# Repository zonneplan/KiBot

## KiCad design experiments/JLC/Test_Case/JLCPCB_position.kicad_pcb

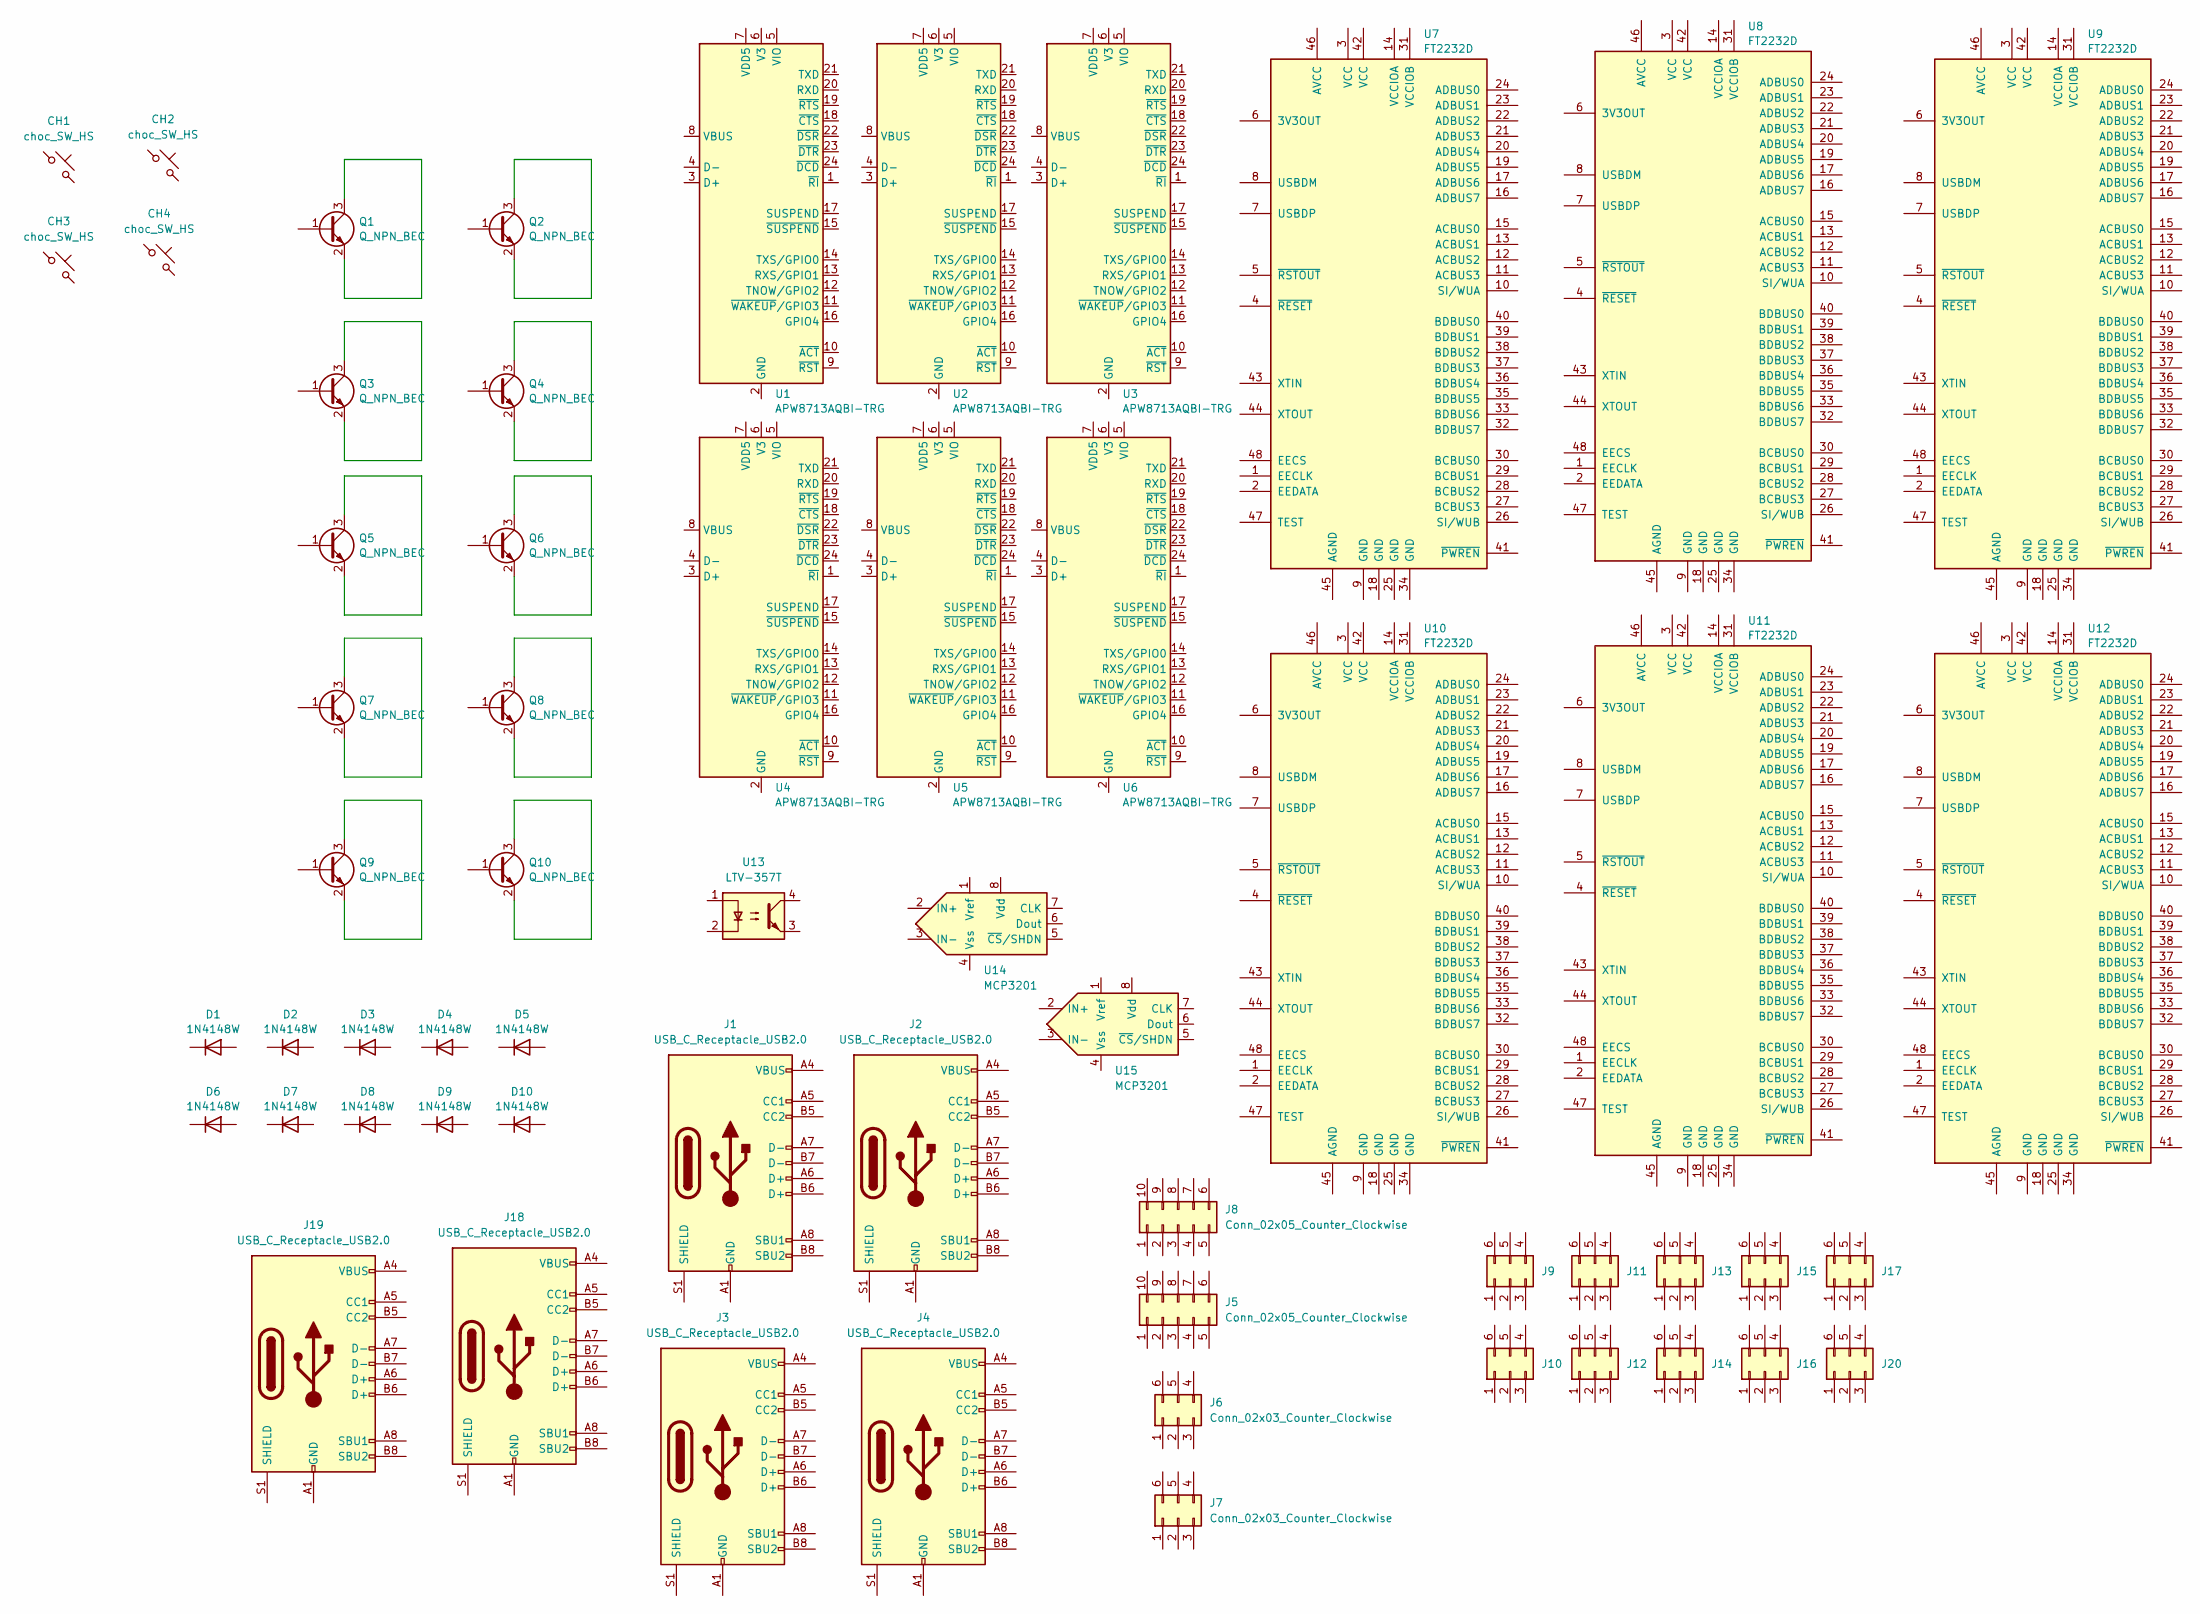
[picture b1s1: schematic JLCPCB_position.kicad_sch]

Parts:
CH1, CH2, CH3, CH4: choc_SW_HS; SW_choc_v1_HS_1u; LCSC C5333465
D1, D2, D3, D4, D5, D6, D7, D8, D9, D10: 1N4148W; D_SOD-123; LCSC C81598
J1, J2, J3, J4, J18, J19: USB_C_Receptacle_USB2.0; USB_C_Receptacle_XKB_U262-16XN-4BVC11; LCSC C319148
J5, J8: Conn_02x05_Counter_Clockwise; PinHeader_2x05_P1.27mm_Vertical; LCSC C2935953
J6, J7, J9, J10, J11, J12, J13, J14, J15, J16, J17, J20: Conn_02x03_Counter_Clockwise; PinHeader_2x03_P1.27mm_Vertical; LCSC C2935951
Q1, Q2, Q3, Q4, Q5, Q6, Q7, Q8, Q9, Q10: Q_NPN_BEC; SOT-23-3; LCSC C8667
U1, U2, U3, U4, U5, U6: APW8713AQBI-TRG; QFN-24-1EP_4x4mm_P0.5mm_EP2.6x2.6mm; LCSC C122485
U7, U8, U9, U10, U11, U12: FT2232D; LQFP-48_7x7mm_P0.5mm; LCSC C428116
U13: LTV-357T; SOP-4_3.8x4.1mm_P2.54mm; LCSC C33068
U14, U15: MCP3201; SOP-8_3.9x4.9mm_P1.27mm; LCSC C49274

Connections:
unnamed: J1.A1 (GND), J1.A12 (GND), J1.B1 (GND), J1.B12 (GND)
unnamed: J1.A4 (VBUS), J1.A9 (VBUS), J1.B4 (VBUS), J1.B9 (VBUS)
unnamed: J2.A1 (GND), J2.A12 (GND), J2.B1 (GND), J2.B12 (GND)
unnamed: J2.A4 (VBUS), J2.A9 (VBUS), J2.B4 (VBUS), J2.B9 (VBUS)
unnamed: J3.A1 (GND), J3.A12 (GND), J3.B1 (GND), J3.B12 (GND)
unnamed: J3.A4 (VBUS), J3.A9 (VBUS), J3.B4 (VBUS), J3.B9 (VBUS)
unnamed: J4.A1 (GND), J4.A12 (GND), J4.B1 (GND), J4.B12 (GND)
unnamed: J4.A4 (VBUS), J4.A9 (VBUS), J4.B4 (VBUS), J4.B9 (VBUS)
unnamed: J18.A1 (GND), J18.A12 (GND), J18.B1 (GND), J18.B12 (GND)
unnamed: J18.A4 (VBUS), J18.A9 (VBUS), J18.B4 (VBUS), J18.B9 (VBUS)
unnamed: J19.A1 (GND), J19.A12 (GND), J19.B1 (GND), J19.B12 (GND)
unnamed: J19.A4 (VBUS), J19.A9 (VBUS), J19.B4 (VBUS), J19.B9 (VBUS)
unnamed: Q1.2 (E), Q1.3 (C)
unnamed: Q2.2 (E), Q2.3 (C)
unnamed: Q3.2 (E), Q3.3 (C)
unnamed: Q4.2 (E), Q4.3 (C)
unnamed: Q5.2 (E), Q5.3 (C)
unnamed: Q6.2 (E), Q6.3 (C)
unnamed: Q7.2 (E), Q7.3 (C)
unnamed: Q8.2 (E), Q8.3 (C)
unnamed: Q9.2 (E), Q9.3 (C)
unnamed: Q10.2 (E), Q10.3 (C)
unnamed: U1.2 (GND), U1.25 (GND)
unnamed: U2.2 (GND), U2.25 (GND)
unnamed: U3.2 (GND), U3.25 (GND)
unnamed: U4.2 (GND), U4.25 (GND)
unnamed: U5.2 (GND), U5.25 (GND)
unnamed: U6.2 (GND), U6.25 (GND)

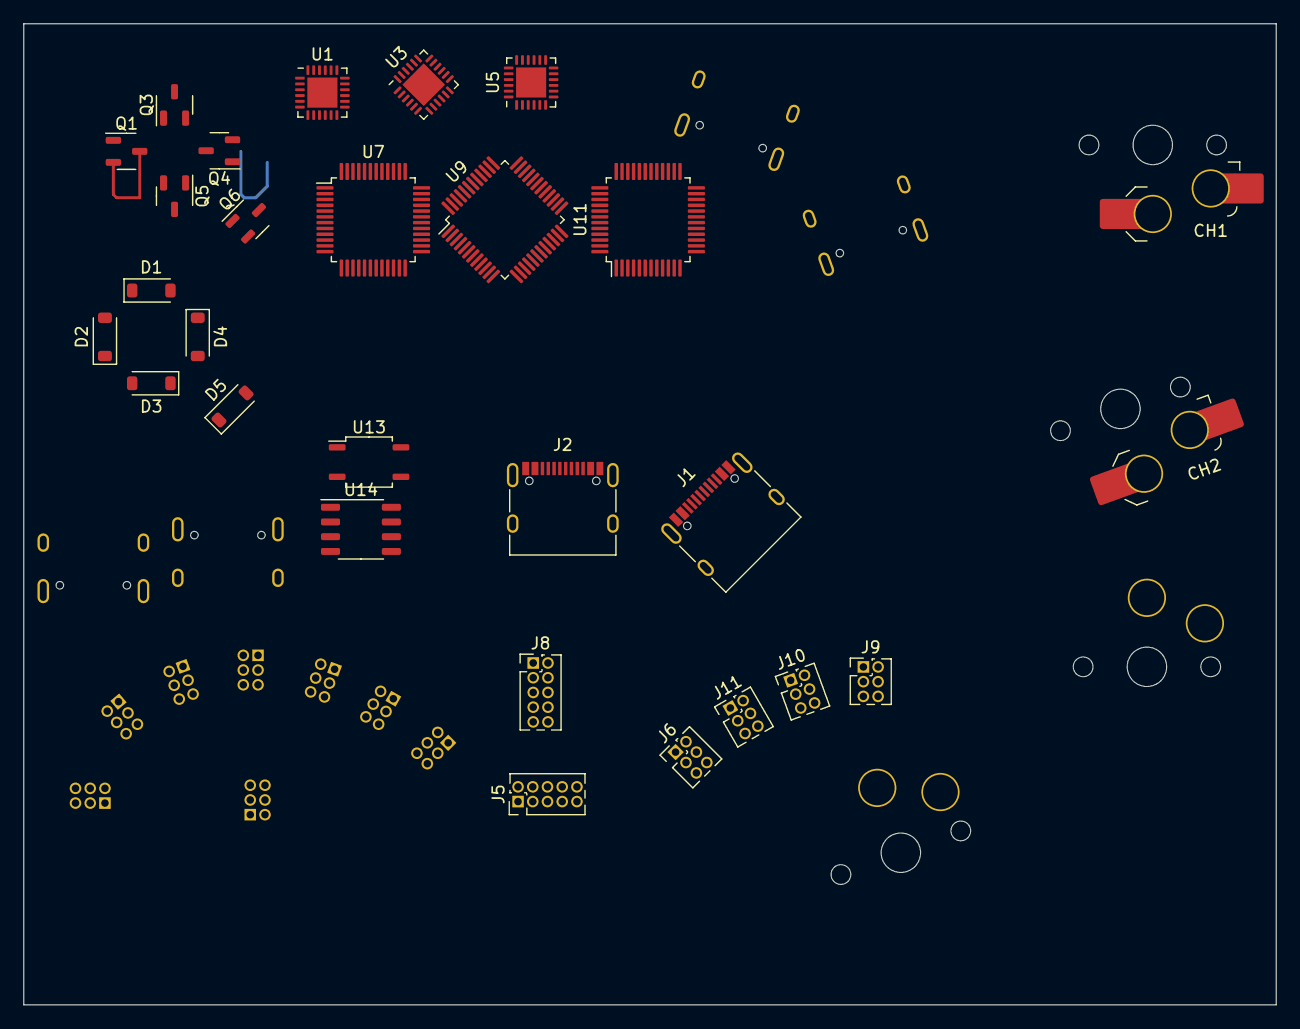
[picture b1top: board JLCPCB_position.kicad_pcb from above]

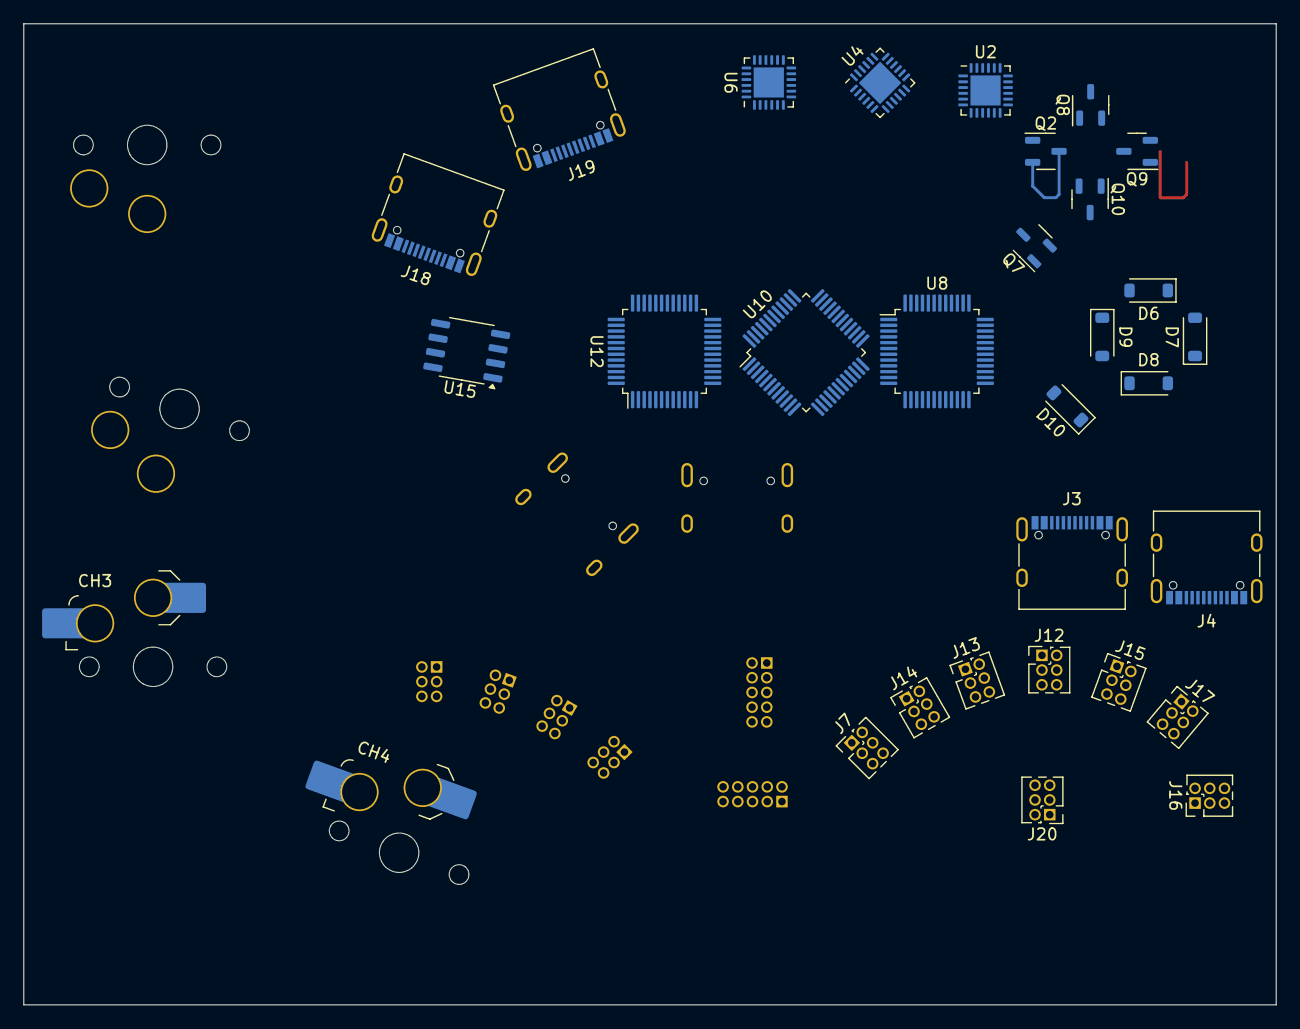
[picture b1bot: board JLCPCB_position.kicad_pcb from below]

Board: 2 copper layers, 108.0 x 84.6 mm, 59 parts (31 on the bottom side), 28 nets.

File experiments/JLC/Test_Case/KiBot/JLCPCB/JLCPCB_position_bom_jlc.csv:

"Comment","Designator","Footprint","LCSC Part #"
"choc_SW_HS","CH1,CH2,CH3,CH4","SW_choc_v1_HS_1u","C5333465"
"1N4148W","D1,D2,D3,D4,D5,D6,D7,D8,D9,D10","D_SOD-123","C81598"
"Conn_02x03_Counter_Clockwise","J6,J7,J9,J10,J11,J12,J13,J14,J15,J16,J17,J20","PinHeader_2x03_P1.27mm_Vertical","C2935951"
"Conn_02x05_Counter_Clockwise","J5,J8","PinHeader_2x05_P1.27mm_Vertical","C2935953"
"USB_C_Receptacle_USB2.0","J1,J2,J3,J4,J18,J19","USB_C_Receptacle_XKB_U262-16XN-4BVC11","C319148"
"Q_NPN_BEC","Q1,Q2,Q3,Q4,Q5,Q6,Q7,Q8,Q9,Q10","SOT-23-3","C8667"
"APW8713AQBI-TRG","U1,U2,U3,U4,U5,U6","QFN-24-1EP_4x4mm_P0.5mm_EP2.6x2.6mm","C122485"
"FT2232D","U7,U8,U9,U10,U11,U12","LQFP-48_7x7mm_P0.5mm","C428116"
"LTV-357T","U13","SOP-4_3.8x4.1mm_P2.54mm","C33068"
"MCP3201","U14,U15","SOP-8_3.9x4.9mm_P1.27mm","C49274"

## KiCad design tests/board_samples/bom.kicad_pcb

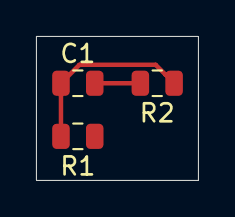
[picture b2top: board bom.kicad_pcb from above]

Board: 2 copper layers, 9.0 x 8.0 mm, 3 parts (0 on the bottom side), 2 nets.

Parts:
C1: 1uF; C_0805_2012Metric
R1: 100; R_0805_2012Metric
R2: 200; R_0805_2012Metric

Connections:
GND: C1.2, R2.2
unnamed: C1.1, R1.2, R2.1

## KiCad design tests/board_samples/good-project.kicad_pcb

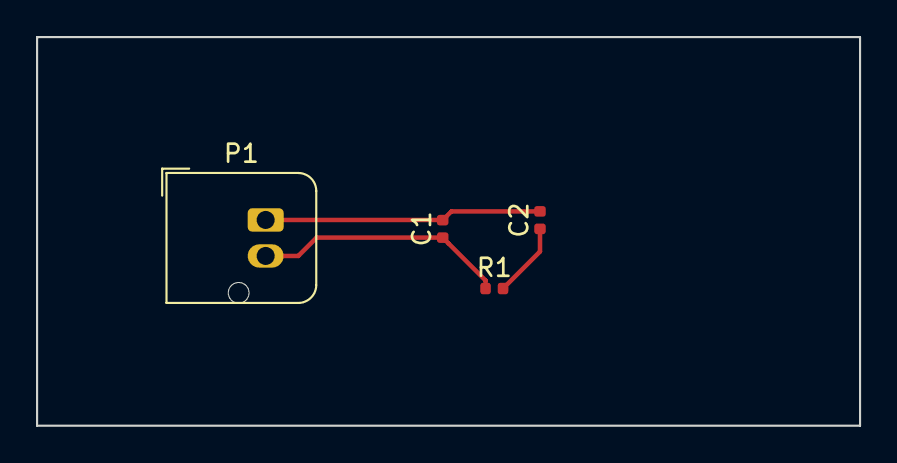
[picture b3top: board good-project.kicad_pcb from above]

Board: 6 copper layers, 45.7 x 21.6 mm, 4 parts (0 on the bottom side), 3 nets.

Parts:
C1, C2: C; C_0402_1005Metric
P1: CONN_01X02; JST_JWPF_B02B-JWPF-SK-R_1x02_P2.00mm_Vertical
R1: R; R_0402_1005Metric

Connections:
/Power/VCC: C1.1, P1.2, R1.1
GND: C1.2, C2.2, P1.1
unnamed: C2.1, R1.2
